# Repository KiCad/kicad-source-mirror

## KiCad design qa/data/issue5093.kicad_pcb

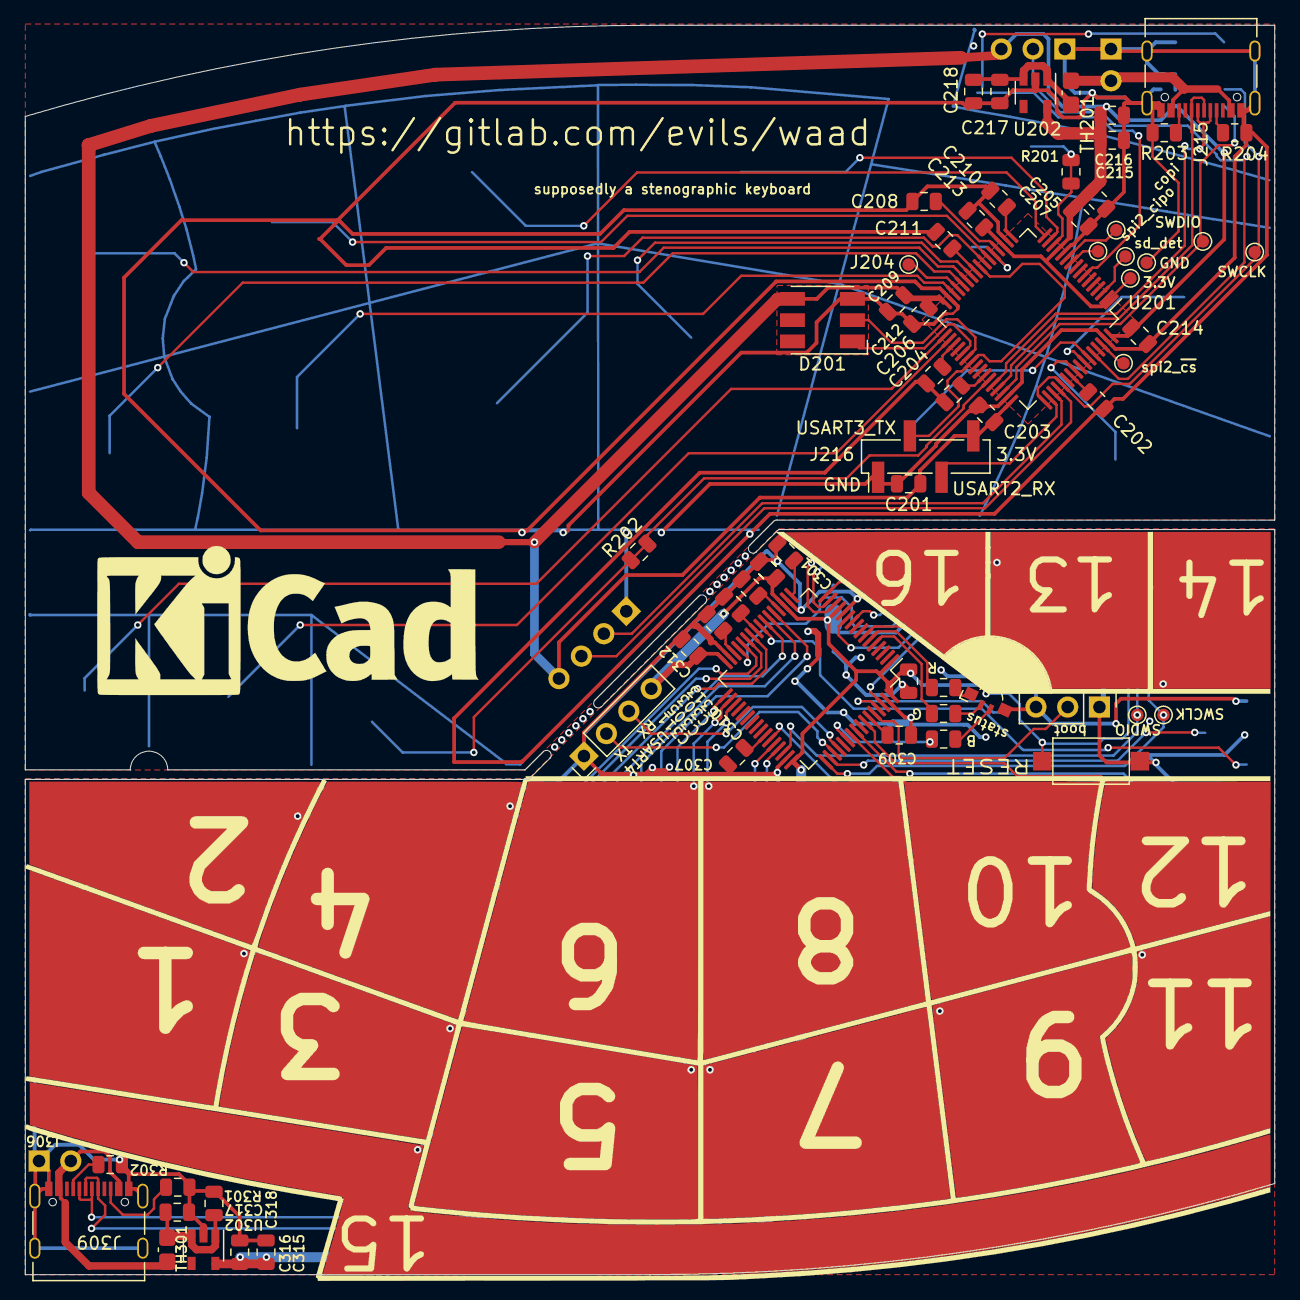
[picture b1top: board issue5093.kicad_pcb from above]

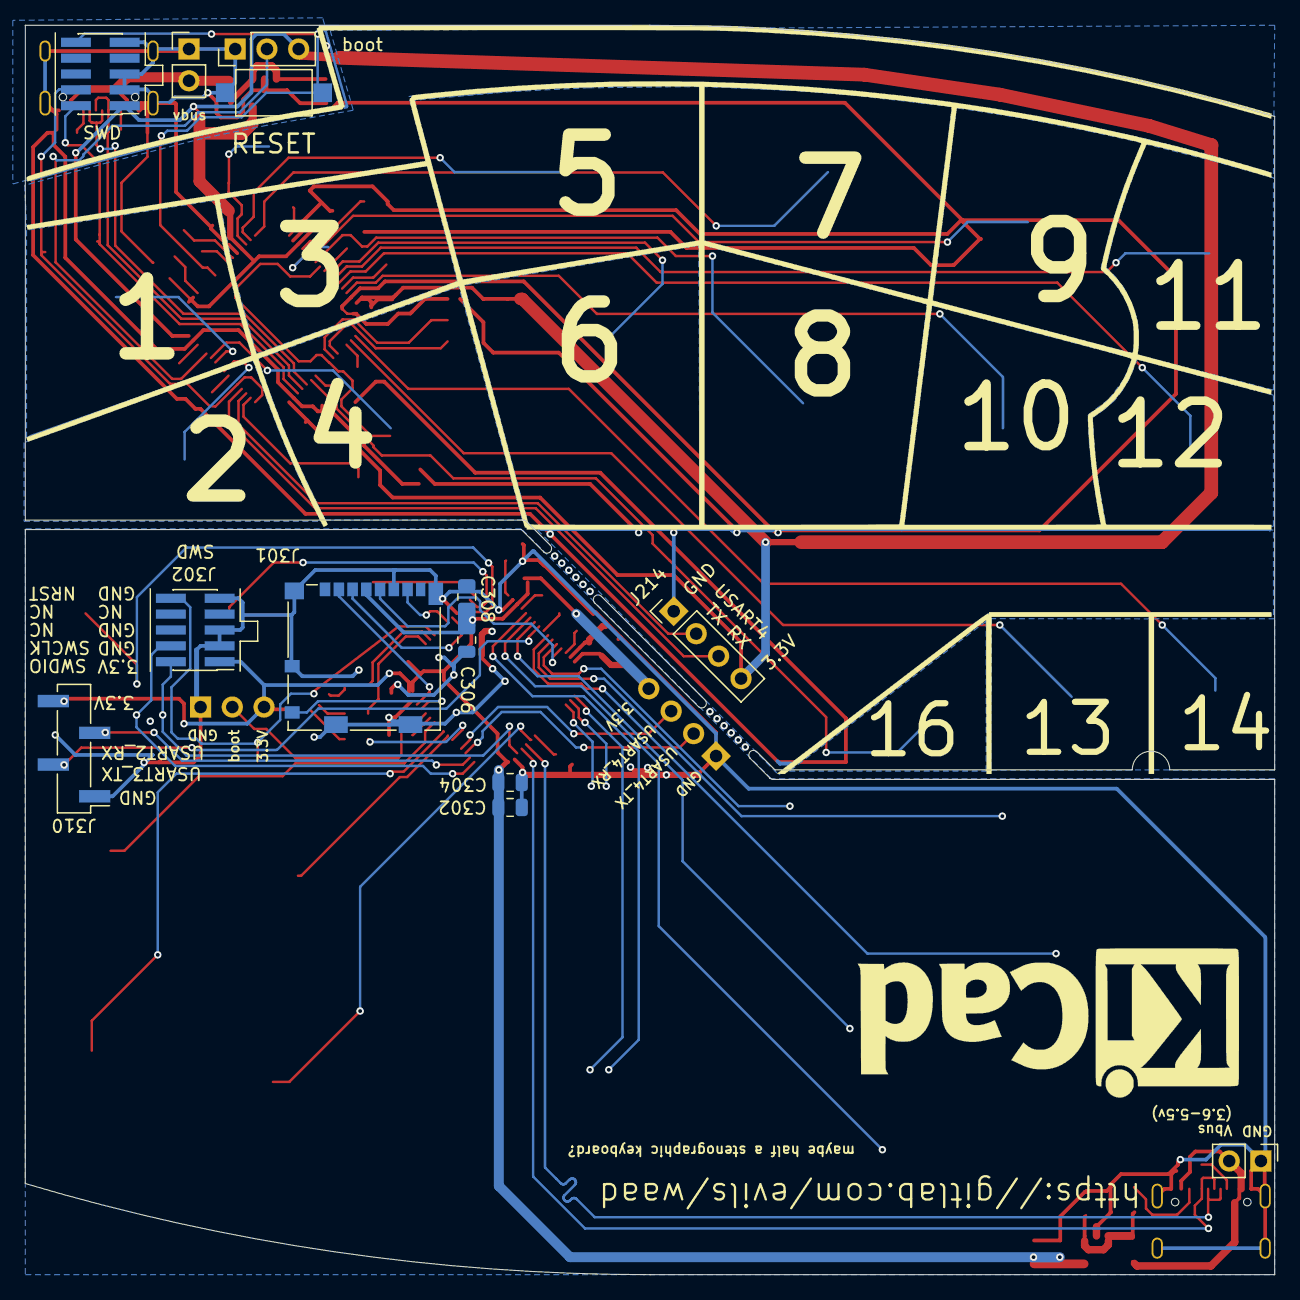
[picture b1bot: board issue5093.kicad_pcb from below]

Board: 2 copper layers, 100.0 x 100.0 mm, 81 parts (14 on the bottom side), 80 nets.

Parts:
C201, C209, C216, C217, C302, C310, C316, C317: 10µF; C_0805_2012Metric
C202, C204, C206, C208, C210, C211, C301, C303, C305, C307, C309, C311: C_Small; C_0805_2012Metric
C203, C205, C212, C213, C214, C304, C306, C312, C313, C314: 1µF; C_0805_2012Metric
C207, C308: 10nF; C_0805_2012Metric
C215, C218, C315, C318: 100µF; C_0805_2012Metric
D201: APA102; LED_RGB_5050-6
D301: LED_RABG; LED_Kingbright_APFA3010_3x1.5mm_Horizontal
J201, J202, J203, J204, J205, J206, J207, J209, J210, J303, J304: Conn_01x01_Male; TestPoint_Pad_D1.0mm
J208, J302: Conn_ARM_JTAG_SWD_10; PinHeader_2x05_P1.27mm_Vertical_SMD
J211: cap_pads; L_borders
J212, J306: Conn_01x02_Male; PinHeader_1x02_P2.54mm_Vertical
J213, J307: Conn_01x03_Male; PinHeader_1x03_P2.54mm_Vertical
J214, J308: Conn_01x04_Male; PinHeader_1x04_P2.54mm_Vertical
J215, J309: USB_C_Receptacle_USB2.0; USB_C_Receptacle_Palconn_UTC16-G
J216, J310: Conn_01x04_Male; PinHeader_1x04_P2.54mm_Vertical_SMD_Pin1Left
J301: Micro_SD_Card_Det; microSD_HC_Molex_104031-0811
J305: cap_pads; R_pads
R201, R202: 1k; R_0805_2012Metric
R203, R204, R301, R302: 5k1; R_0805_2012Metric
R303: 50; R_0805_2012Metric
R304, R305: 5; R_0805_2012Metric
SW201, SW301: SW_Push; SW_SPST_CK_RS282G05A3
TH201, TH301: Thermistor_PTC; Fuse_0805_2012Metric_Castellated
U201, U301: STM32F072R8Tx; LQFP-64_10x10mm_P0.5mm
U202, U302: TLV75533PDBV; SOT-23-5

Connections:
/left/+3V3: C201.1, C203.1, C205.1, C207.1, C209.1, C212.1, C213.1, C214.1, C215.1, C216.1, D201.4 (VCC), J203.1, J208.1 (VTref), J213.3, J214.4, J216.4, U201.1 (VBAT), U201.2 (PC13), U201.13 (VDDA), U201.19 (VDD), U201.32 (VDD), U201.48 (VDDIO2), U201.64 (VDD), U202.5 (OUT)
/left/APA_CI: D201.2 (CI), U201.38 (PC7)
/left/APA_DI: D201.1 (DI), U201.37 (PC6)
/left/BOOT0: J213.2, U201.60 (BOOT0)
/left/D+: J215.A6 (D+), J215.B6 (D+), U201.45 (PA12)
/left/D-: J215.A7 (D-), J215.B7 (D-), U201.44 (PA11)
/left/GND: C201.2, C202.2, C203.2, C204.2, C205.2, C206.2, C207.2, C208.2, C209.2, C210.2, C211.2, C212.2, C213.2, C214.2, C215.2, C216.2, C217.2, C218.2, D201.3 (GND), J205.1, J208.3 (GND), J208.5 (GND), J208.9 (GNDDetect), J212.1, J213.1, J214.1, J215.A1 (GND), J215.A12 (GND), J215.B1 (GND), J215.B12 (GND), J215.S1 (SHIELD), J216.1, R203.2, R204.2, SW201.1, U201.12 (VSSA), U201.18 (VSS), U201.31 (VSS), U201.47 (VSS), U201.63 (VSS), U202.2 (GND)
/left/NRST: J208.10 (~RESET~), SW201.2, U201.7 (NRST)
/left/P14: R201.1, R201.2, U201.14 (PA0)
/left/P17: C210.1, U201.17 (PA3)
/left/P20: C208.1, U201.20 (PA4)
/left/P25: C211.1, U201.25 (PC5)
/left/P35: C206.1, U201.35 (PB14)
/left/P42: C204.1, U201.42 (PA9)
/left/P43: R202.1, R202.2, U201.43 (PA10)
/left/P55: C202.1, U201.55 (PB3)
/left/SD_DET: J207.1, U201.3 (PC14)
/left/SPI2_CIPO: J206.1, U201.10 (PC2)
/left/SPI2_COPI: J202.1, U201.11 (PC3)
/left/SPI2_SCK: J204.1, U201.29 (PB10)
/left/SPI2_~CS: J201.1, U201.62 (PB9)
/left/SWCLK: J208.4 (SWDCLK/TCK), J210.1, U201.49 (PA14), U201.53 (PC12)
/left/SWDIO: J208.2 (SWDIO/TMS), J209.1, U201.46 (PA13)
/left/USART2_RX: J216.3, U201.50 (PA15)
/left/USART3_TX: J216.2, U201.24 (PC4), U201.39 (PC8)
/left/USART4_RX: J214.3, U201.52 (PC11)
/left/USART4_TX: J214.2, U201.51 (PC10)
/left/VBUS: J212.2, J215.A4 (VBUS), J215.A9 (VBUS), J215.B4 (VBUS), J215.B9 (VBUS), TH201.2
/right/+3V3: C302.1, C304.1, C306.1, C308.1, C310.1, C312.1, C313.1, C314.1, C315.1, C316.1, D301.2 (A), J301.4 (VDD), J302.1 (VTref), J307.3, J308.4, J310.4, U301.1 (VBAT), U301.13 (VDDA), U301.19 (VDD), U301.32 (VDD), U301.48 (VDDIO2), U301.64 (VDD), U302.5 (OUT)
/right/BOOT0: J307.2, U301.60 (BOOT0)
/right/D+: J309.A6 (D+), J309.B6 (D+), U301.45 (PA12)
/right/D-: J309.A7 (D-), J309.B7 (D-), U301.44 (PA11)
/right/GND: C301.2, C302.2, C303.2, C304.2, C305.2, C306.2, C307.2, C308.2, C309.2, C310.2, C311.2, C312.2, C313.2, C314.2, C315.2, C316.2, C317.2, C318.2, J301.6 (VSS), J301.9 (DET_B), J301.11 (SHIELD), J302.3 (GND), J302.5 (GND), J302.9 (GNDDetect), J306.1, J307.1, J308.1, J309.A1 (GND), J309.A12 (GND), J309.B1 (GND), J309.B12 (GND), J309.S1 (SHIELD), J310.1, R301.2, R302.2, SW301.1, U301.12 (VSSA), U301.18 (VSS), U301.31 (VSS), U301.47 (VSS), U301.63 (VSS), U302.2 (GND)
/right/LED_B: R305.1, U301.54 (PD2)
/right/LED_G: R304.1, U301.5 (PF0)
/right/LED_R: R303.1, U301.6 (PF1)
/right/NRST: J302.10 (~RESET~), SW301.2, U301.7 (NRST)
/right/P14: J305.14, U301.14 (PA0)
/right/P15: J305.13, U301.15 (PA1)
/right/P16: J305.16, U301.16 (PA2)
/right/P17: C301.1, U301.17 (PA3)
/right/P20: C303.1, U301.20 (PA4)
/right/P21: J305.5, U301.21 (PA5)
/right/P22: J305.15, U301.22 (PA6)
/right/P23: J305.3, U301.23 (PA7)
/right/P25: C305.1, U301.25 (PC5)
/right/P26: J305.1, U301.26 (PB0)
/right/P27: J305.2, U301.27 (PB1)
/right/P28: J305.4, U301.28 (PB2)
/right/P30: C311.1, U301.30 (PB11)
/right/P33: J305.7, U301.33 (PB12)
/right/P34: J305.6, U301.34 (PB13)
/right/P35: J305.8, U301.35 (PB14)
/right/P42: C307.1, U301.42 (PA9)
/right/P43: J305.9, U301.43 (PA10)
/right/P55: J305.10, U301.55 (PB3)
/right/P56: J305.11, U301.56 (PB4)
/right/P58: J305.12, U301.58 (PB6)
/right/P59: C309.1, U301.59 (PB7)
/right/SD_DET: J301.10 (DET_A), U301.61 (PB8)
/right/SPI2_CIPO: J301.7 (DAT0), U301.10 (PC2)
/right/SPI2_COPI: J301.3 (CMD), U301.11 (PC3)
/right/SPI2_SCK: J301.5 (CLK), U301.29 (PB10)
/right/SPI2_~CS: J301.2 (DAT3/CD), U301.62 (PB9)
/right/SWCLK: J302.4 (SWDCLK/TCK), J304.1, U301.49 (PA14)
/right/SWDIO: J302.2 (SWDIO/TMS), J303.1, U301.46 (PA13)
/right/USART2_RX: J310.3, U301.50 (PA15)
/right/USART3_TX: J310.2, U301.24 (PC4)
/right/USART4_RX: J308.3, U301.52 (PC11)
/right/USART4_TX: J308.2, U301.51 (PC10)
/right/VBUS: J306.2, J309.A4 (VBUS), J309.A9 (VBUS), J309.B4 (VBUS), J309.B9 (VBUS), TH301.2
unnamed: C217.1, C218.1, TH201.1, U202.1 (IN), U202.3 (EN)
unnamed: C317.1, C318.1, TH301.1, U302.1 (IN), U302.3 (EN)
unnamed: D301.1 (RK), R303.2
unnamed: D301.3 (BK), R305.2
unnamed: D301.4 (GK), R304.2
unnamed: J215.A5 (CC1), R204.1
unnamed: J215.B5 (CC2), R203.1
unnamed: J309.A5 (CC1), R302.1
unnamed: J309.B5 (CC2), R301.1

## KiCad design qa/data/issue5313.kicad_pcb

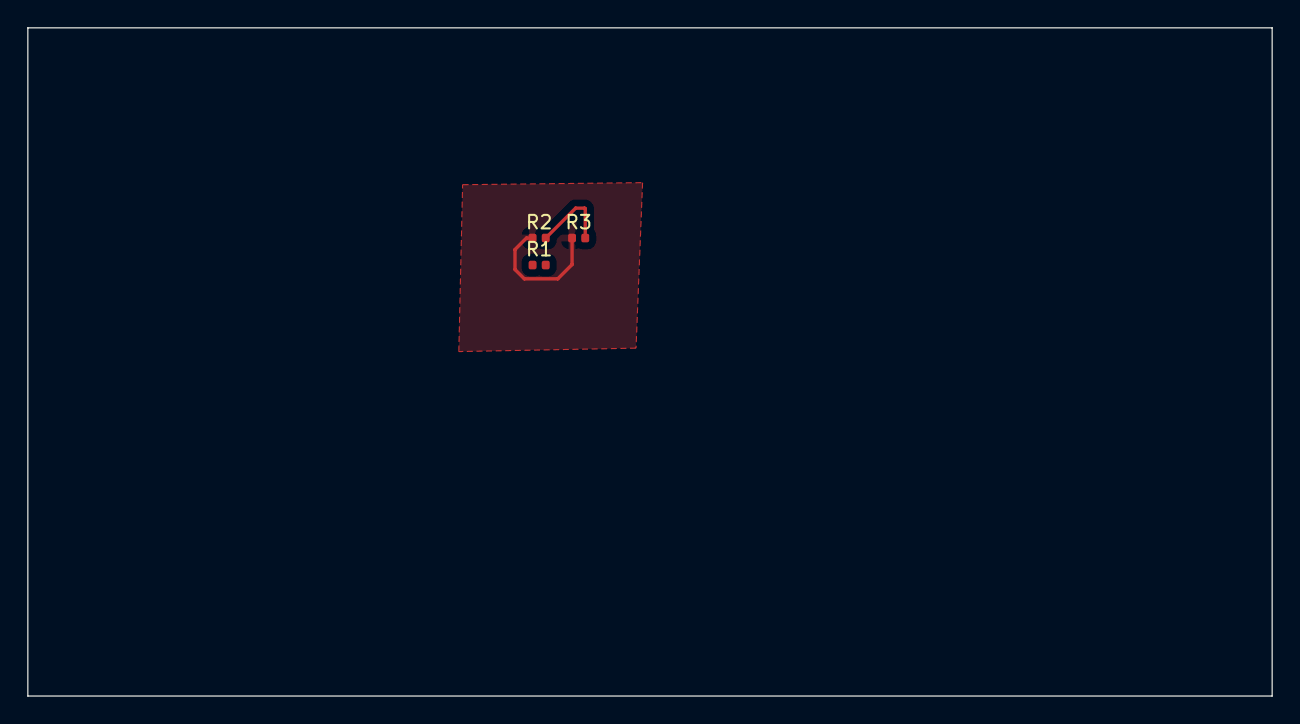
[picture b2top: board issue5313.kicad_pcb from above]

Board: 2 copper layers, 91.7 x 49.2 mm, 3 parts (0 on the bottom side), 2 nets.

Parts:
R1, R2, R3: R_Small; R_0402_1005Metric

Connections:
unnamed: R1.2, R2.2, R3.2
unnamed: R2.1, R3.1

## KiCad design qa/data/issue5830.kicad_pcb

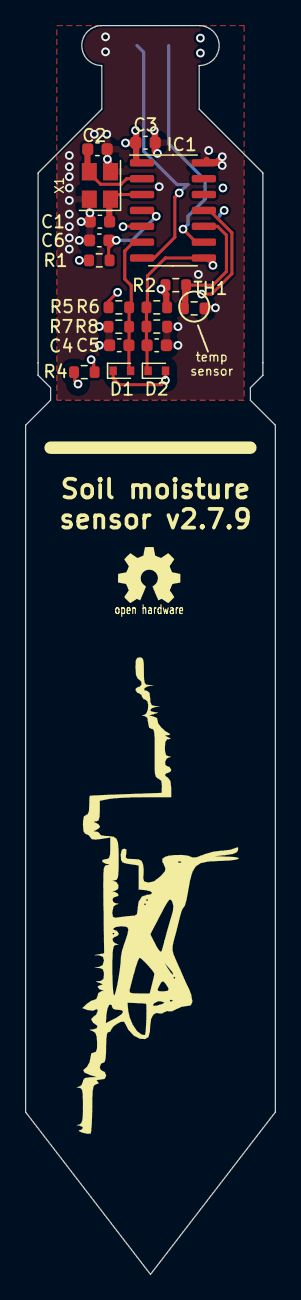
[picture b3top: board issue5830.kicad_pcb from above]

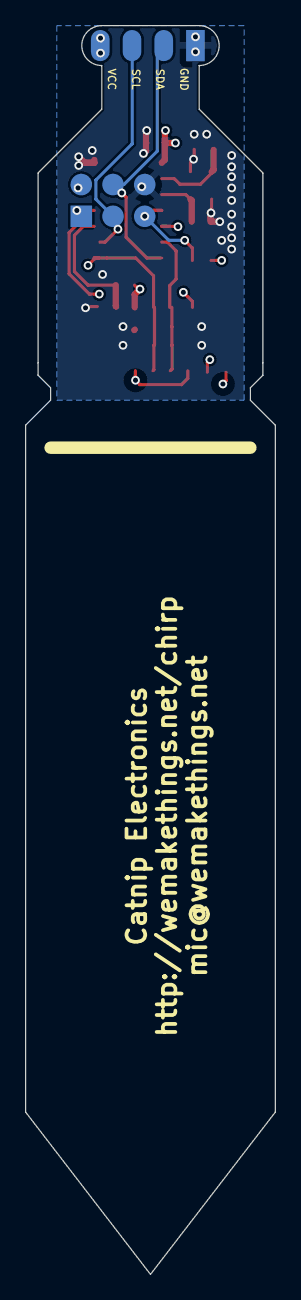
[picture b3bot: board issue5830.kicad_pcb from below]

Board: 4 copper layers, 20.0 x 100.0 mm, 20 parts (2 on the bottom side), 13 nets.

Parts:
C1: 33p; C_0603_1608Metric
C2: 33pp; C_0603_1608Metric
C3, C6: 1u; C_0603_1608Metric
C4, C5: 1n; C_0603_1608Metric
D1, D2: BAT54; D_SOD-523
IC1: ATTINY441-SSU; SOIC-14_3.9x8.7mm_P1.27mm
P1: CONN_02X03; Pin_Header_Straight_2x03
P2: CONN_01X04; Pin_Header_Straight_1x04_Pitch2.54mm
R1: 10k; R_0603_1608Metric
R2: 10k 0.1%; R_0603_1608Metric
R4: 330; R_0603_1608Metric
R5, R6, R7, R8: 1M; R_0603_1608Metric
TH1: NCP18XH103F03RB; R_0603_1608Metric
X1: 16MHz; Crystal_SMD_3225-4pin_3.2x2.5mm

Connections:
/EXCITATION: IC1.5, R4.2
/MISO/SENSE_HIGH: C5.1, D2.2, IC1.8, P1.1, R6.1, R8.2
/MOSI/SDA: IC1.7, P1.4, P2.2
/RESET: C6.1, IC1.4, P1.5, R1.1
/SCK/SCL: IC1.9, P1.3, P2.3
/SENSE_LOW: C4.1, D1.1, IC1.6, R5.1, R7.2
/SENSOR_TRACK: D1.2, D2.1, R4.1
/THERMISTOR: IC1.10, R2.2, TH1.1
GND: C1.2, C2.2, C3.2, C4.2, C5.2, C6.2, IC1.14, P1.6, P2.1, R7.1, R8.1, TH1.2, X1.2, X1.4
unnamed: C1.1, IC1.3, X1.1
unnamed: C2.1, IC1.2, X1.3
unnamed: IC1.11, R2.1, R5.2, R6.2
VCC: C3.1, IC1.1, P1.2, P2.4, R1.2

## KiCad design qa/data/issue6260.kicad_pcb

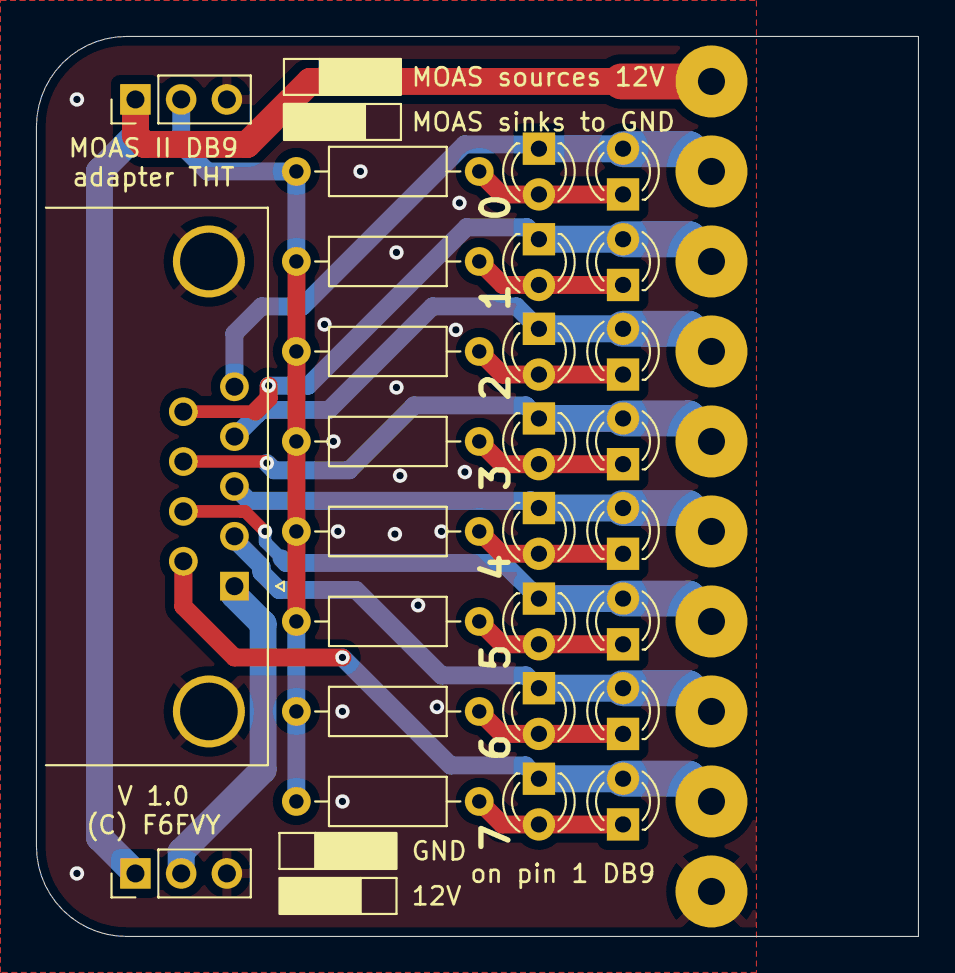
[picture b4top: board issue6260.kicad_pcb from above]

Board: 2 copper layers, 49.0 x 50.0 mm, 37 parts (0 on the bottom side), 20 nets.

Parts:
D1, D2, D3, D4, D5, D6, D7, D8, D9, D10, D11, D12, D13, D14, D15, D16: LED; LED_D3.0mm
J1, J2, J3, J4, J5, J6, J7, J8, J9, J10: Conn_01x01; SolderWirePad_1x01_Drill1.5mm
J11, J12: Conn_01x03; PinHeader_1x03_P2.54mm_Vertical
J13: DB9_Female_MountingHoles; DSUB-9_Female_Horizontal_P2.77x2.84mm_EdgePinOffset7.70mm_H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
R1, R2, R3, R4, R5, R6, R7, R8: 4k7; R_Axial_DIN0207_L6.3mm_D2.5mm_P10.16mm_Horizontal

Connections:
+12V: J1.1, J11.1, J12.1
GND: J10.1, J11.3, J12.3, J13.0 (PAD)
unnamed: D1.1 (K), D9.2 (A), J2.1, J13.5
unnamed: D1.2 (A), D9.1 (K), R1.1
unnamed: D2.2 (A), D10.1 (K), R2.1
unnamed: D2.1 (K), D10.2 (A), J3.1, J13.9
unnamed: D3.2 (A), D11.1 (K), R3.1
unnamed: D3.1 (K), D11.2 (A), J4.1, J13.4
unnamed: D4.2 (A), D12.1 (K), R4.1
unnamed: D4.1 (K), D12.2 (A), J5.1, J13.8
unnamed: D5.2 (A), D13.1 (K), R5.1
unnamed: D5.1 (K), D13.2 (A), J6.1, J13.3
unnamed: D6.2 (A), D14.1 (K), R6.1
unnamed: D6.1 (K), D14.2 (A), J7.1, J13.7
unnamed: D7.2 (A), D15.1 (K), R7.1
unnamed: D7.1 (K), D15.2 (A), J8.1, J13.2
unnamed: D8.2 (A), D16.1 (K), R8.1
unnamed: D8.1 (K), D16.2 (A), J9.1, J13.6
unnamed: J11.2, R1.2, R2.2, R3.2, R4.2, R5.2, R6.2, R7.2, R8.2
unnamed: J12.2, J13.1

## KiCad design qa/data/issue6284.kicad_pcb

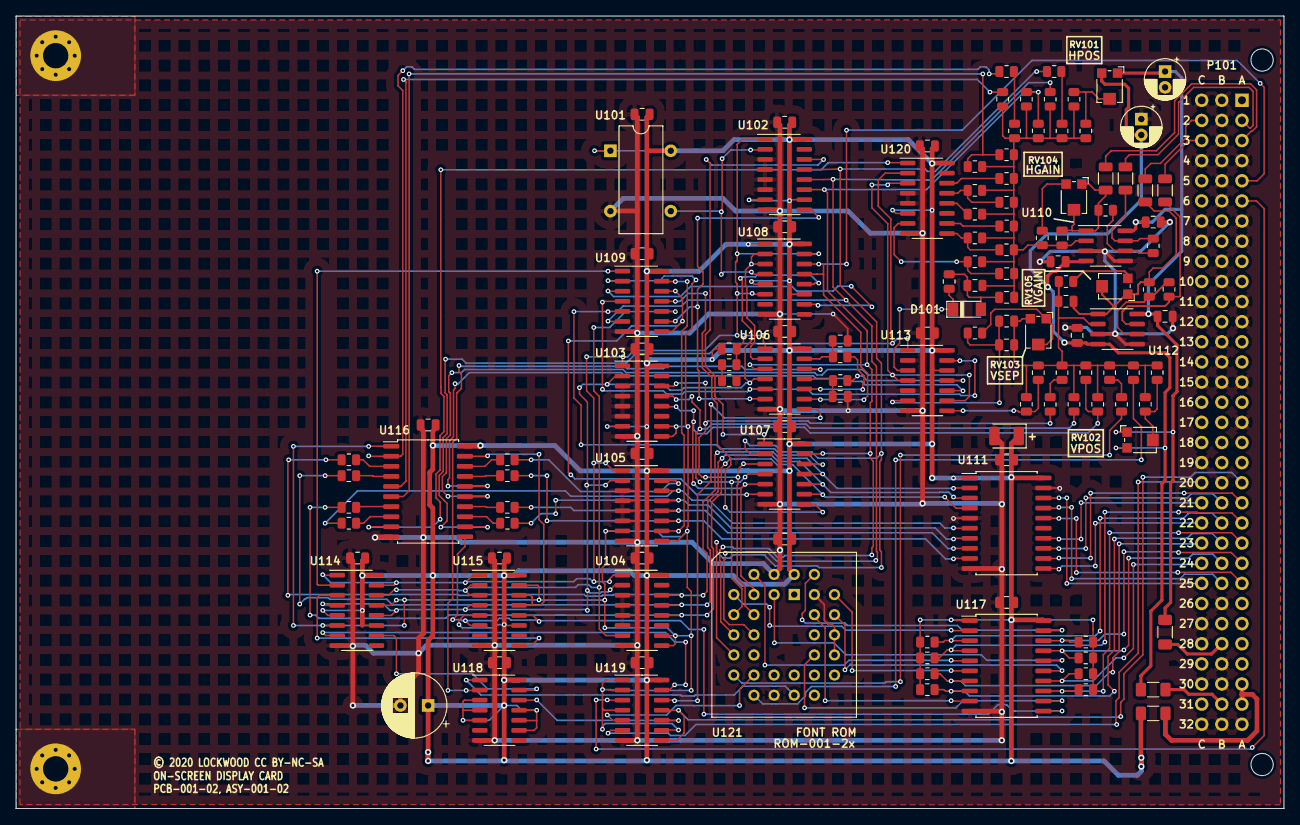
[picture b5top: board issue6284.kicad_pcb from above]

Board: 2 copper layers, 160.0 x 100.0 mm, 134 parts (0 on the bottom side), 127 nets.

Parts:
C101, C104, C105, C106, C108: 100p; C_0805_2012Metric
C102, C103: 47p; C_0805_2012Metric
C107, C109, C110: 330p; C_0805_2012Metric
CD101: 470µ; CP_Radial_D8.0mm_P3.50mm
CD102: 10µ; CP_EIA-3528-21_Kemet-B
CD103, CD104, CD105, CD106, CD107, CD108, CD109, CD110, CD111, CD112, CD113, CD114, CD115, CD116, CD117, CD118, CD119, CD120, CD121, CD123, CD124, CD126, CD127: 1µ; C_0805_2012Metric
CD122, CD125: 47µ; CP_Radial_D5.0mm_P2.00mm
D101: LL4448; D_MiniMELF
H101, H102: HOLE; MountingHole_3.2mm_M3_Pad_Via
P101: DIN41612_M_3x32_OS2; DIN41612_B_3x32_Horizontal
R101, R102, R103, R104, R105, R106, R107, R108, R155, R156: 2k37; R_0805_2012Metric
R109, R110, R112, R113, R114, R115, R116, R117, R118, R119, R128, R133, R137, R142, R143, R147, R148, R149, R150, R151: 39k; R_0805_2012Metric
R111, R120, R123, R125, R126: 1k96; R_0805_2012Metric
R121, R136: 680k; R_0805_2012Metric
R122, R129, R130, R131, R138, R152, R153, R154: 205k; R_0805_2012Metric
R124, R134, R135, R157, R158, R159, R160: 5k9; R_0805_2012Metric
R127, R132, R144, R145, R146: 274k; R_0805_2012Metric
R139, R140, R141: 9k76; R_0805_2012Metric
R161, R162, R163, R164: 1k5; R_1206_3216Metric
RT101, RT102, RT103: 250mA; R_1206_3216Metric_Pad1.30x1.75mm_HandSolder
RV101, RV102: 20k; Potentiometer_Bourns_TC33X_Vertical
RV103: 1k; Potentiometer_Bourns_TC33X_Vertical
RV104, RV105: 500; Potentiometer_Bourns_TC33X_Vertical
U101: 2MHz; Oscillator_SeikoEpson_SG-8002DC
U102, U103, U104, U105: 'HC161; SOIC-16_3.9x9.9mm_P1.27mm
U106: 'HC14; SOIC-14_3.9x8.7mm_P1.27mm
U107, U118: 'HC10; SOIC-14_3.9x8.7mm_P1.27mm
U108, U114, U115: 'HC109; SOIC-16_3.9x9.9mm_P1.27mm
U109: 'HC02; SOIC-14_3.9x8.7mm_P1.27mm
U110, U112: NE5532; SOIC-8_3.9x4.9mm_P1.27mm
U111: 'HC245; SOIC-20W_7.5x12.8mm_P1.27mm
U113: 'HC86; SOIC-14_3.9x8.7mm_P1.27mm
U116, U117: 'HCT273; SOIC-20W_7.5x12.8mm_P1.27mm
U119: 'HC03; SOIC-14_3.9x8.7mm_P1.27mm
U120: 'HC237; SOIC-16_3.9x9.9mm_P1.27mm
U121: 27C512; PLCC-32_THT-Socket

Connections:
+15V: CD122.1, CD123.1, CD124.1, RT101.2, RV101.1, RV102.1, U110.8 (V+), U112.8 (V+)
-15V: CD125.2, CD126.1, CD127.1, RT103.2, RV101.3, RV102.3, U110.4 (V-), U112.4 (V-)
/CHAR0: P101.B22 (CHAR0), R108.2, U117.3 (D0)
/CHAR1: P101.A22 (CHAR1), R107.2, U117.4 (D1)
/CHAR2: P101.C23 (CHAR2), R106.2, U117.7 (D2)
/CHAR3: P101.B23 (CHAR3), R105.2, U117.8 (D3)
/CHAR4: P101.A23 (CHAR4), R104.2, U117.13 (D4)
/CHAR5: P101.C24 (CHAR5), R103.2, U117.14 (D5)
/CHAR6: P101.B24 (CHAR6), R102.2, U117.17 (D6)
/CHAR7: P101.A24 (CHINT), R101.2, U117.18 (D7)
/Circuit/CHAR0: U117.2 (Q0), U121.5 (A6)
/Circuit/CHAR1: U117.5 (Q1), U121.4 (A7)
/Circuit/CHAR2: U117.6 (Q2), U121.29 (A8)
/Circuit/CHAR3: U117.9 (Q3), U121.28 (A9)
/Circuit/CHAR4: U117.12 (Q4), U121.24 (A10)
/Circuit/CHAR5: U117.15 (Q5), U121.27 (A11)
/Circuit/CHAR6: U117.16 (Q6), U121.3 (A12)
/Circuit/CHAR7: U117.19 (Q7), U121.30 (A13)
/Circuit/DESCENDER0: R129.2, U121.13 (O0)
/Circuit/DESCENDER1: R138.2, U121.14 (O1)
/Circuit/FINISH#: U114.3 (~K), U115.9 (~Q)
/Circuit/FINISHREQ: R119.2, U105.15 (Tc)
/Circuit/FLD0: U116.9 (Q3), U120.1 (A0)
/Circuit/FLD1: U113.1, U116.12 (Q4), U120.2 (A1)
/Circuit/FLD2: U113.4, U113.9, U116.15 (Q5), U120.3 (A2)
/Circuit/FLD3: U113.10, U116.16 (Q6)
/Circuit/FLDREQ0: R115.2, U105.14 (Q0), U111.6 (A4)
/Circuit/FLDREQ1: R116.2, U105.13 (Q1), U111.7 (A5)
/Circuit/FLDREQ2: R117.2, U105.12 (Q2), U111.8 (A6)
/Circuit/FLDREQ3: R118.2, U105.11 (Q3), U111.9 (A7)
/Circuit/FLD_BOTTOM: R136.1, R137.2, U113.8
/Circuit/HDOT0: R127.2, U102.13 (Q1), U107.2, U121.11 (A0)
/Circuit/HDOT1: R132.2, U102.12 (Q2), U109.6, U121.10 (A1)
/Circuit/HDOT2: R145.2, R146.2, U102.11 (Q3), U106.3, U107.13, U121.9 (A2)
/Circuit/INTEN: U119.5, U121.15 (O2)
/Circuit/INTERLINE_BLANK#: U106.12, U118.2
/Circuit/LASTDOT: U106.5, U109.4, U113.13
/Circuit/LATCHBUS: U115.6 (Q), U115.12 (C), U116.11 (Cp), U117.11 (Cp)
/Circuit/LINE0: R122.2, U103.14 (Q0), U107.3, U121.8 (A3)
/Circuit/LINE1: R153.2, U103.13 (Q1), U107.4, U121.7 (A4)
/Circuit/LINE2: R130.2, R131.2, U103.12 (Q2), U107.5, U121.6 (A5)
/Circuit/NEXTFLDREQ: U105.10 (ENT), U109.13
/Circuit/NEXTPOSREQ: U104.7 (ENP), U109.10, U114.14 (J), U115.2 (J), U115.3 (~K)
/Circuit/PIX_BLANK#: U118.1, U121.18 (O3)
/Circuit/POS0: R128.2, U116.2 (Q0)
/Circuit/POS1: R133.2, U116.5 (Q1)
/Circuit/POS2: R148.2, R149.2, U116.6 (Q2)
/Circuit/POSREQ0: R112.2, U104.14 (Q0), U107.11, U111.2 (A0)
/Circuit/POSREQ1: R113.2, U104.13 (Q1), U107.10, U111.3 (A1)
/Circuit/POSREQ2: R114.2, U104.12 (Q2), U107.9, U111.4 (A2)
/Circuit/READY: U114.10 (Q), U118.13
/Circuit/STARTCMD: U106.8, U119.12
/Circuit/~LASTDOT: U102.9 (~Pe), U106.6, U109.9
/Circuit/~LASTLINE: U107.6, U109.8, U109.12
/Circuit/~LASTPOSREQ: U107.8, U109.11
/FLD0: P101.C21 (SA12), U111.14 (B4)
/FLD1: P101.B21 (SA13), U111.13 (B5)
/FLD2: P101.A21 (SA14), U111.12 (B6)
/FLD3: P101.C22 (SA15), U111.11 (B7)
/H+: P101.A2 (TS+), R162.2
/H-: P101.A3 (TS-), R161.2
/INTEN#: P101.C20 (SA10), U119.6
/POS0: P101.C25 (POS0), U111.18 (B0)
/POS1: P101.B25 (POS1), U111.17 (B1)
/POS2: P101.A25 (POS2), U111.16 (B2)
/RUN#: P101.A6 (SS1), U119.3
/START#: P101.A5 (SS0), U106.9, U108.13 (~K), U108.14 (J)
/V+: P101.C2 (SIG+), R163.2
/V-: P101.C3 (SIG-), R164.2
/ZSEL: P101.A20 (SA11), U119.8, U119.11
DONE: U114.7 (~Q), U119.13
DOTCLK: U101.5 (OUT), U102.2 (CK), U108.4 (C)
GND: C102.2, C103.2, CD101.2, CD102.2, CD103.2, CD104.2, CD105.2, CD106.2, CD107.2, CD108.2, CD109.2, CD110.2, CD111.2, CD112.2, CD113.2, CD114.2, CD115.2, CD116.2, CD117.2, CD118.2, CD119.2, CD120.2, CD121.2, CD122.2, CD123.2, CD124.2, CD125.1, CD126.2, CD127.2, H101.1, H102.1, P101.A1 (GND), P101.A4 (GND), P101.A7 (GND), P101.A8 (GND), P101.A11 (GND), P101.A12 (GND), P101.A15 (GND), P101.A17 (GND), P101.A32 (GND), P101.B1 (GND), P101.B2 (GND), P101.B3 (GND), P101.B4 (GND), P101.B5 (GND), P101.B6 (GND), P101.B9 (GND), P101.B10 (GND), P101.B13 (GND), P101.B14 (GND), P101.B15 (GND), P101.B20 (GND), P101.B26 (GND), P101.B29 (GND), P101.B30 (GND), P101.B32 (GND), P101.C1 (GND), P101.C4 (GND), P101.C7 (GND), P101.C8 (GND), P101.C11 (GND), P101.C12 (GND), P101.C15 (GND), P101.C19 (GND), P101.C27 (GND), P101.C28 (GND), P101.C30 (GND), P101.C32 (GND), R110.2, U101.4 (GND), U102.3 (P0), U102.4 (P1), U102.5 (P2), U102.6 (P3), U102.8 (GND), U103.3 (P0), U103.4 (P1), U103.5 (P2), U103.6 (P3), U103.8 (GND), U104.3 (P0), U104.4 (P1), U104.5 (P2), U104.6 (P3), U104.8 (GND), U105.3 (P0), U105.4 (P1), U105.5 (P2), U105.6 (P3), U105.8 (GND), U106.7 (GND), U107.7 (GND), U108.8 (GND), U109.7 (GND), U110.3 (+), U110.5 (+), U111.5 (A3), U111.10 (GND), U111.19 (CE), U112.3 (+), U112.5 (+), U113.2, U113.5, U113.7 (GND), U114.8 (GND), U115.8 (GND), U116.10 (GND), U117.10 (GND), U118.7 (GND), U119.7 (GND), U120.4 (~LE), U120.5 (~E1), U120.8 (GND), U121.2 (A15), U121.16 (GND), U121.23 (~CE), U121.25 (~OE~/VPP), U121.31 (A14)
unnamed: C101.2, R109.1, U106.1
unnamed: C102.1, R111.1, U106.11
unnamed: C103.1, R120.1, U106.13
unnamed: C104.1, R126.2, U120.7 (Y7)
unnamed: C104.2, C107.2, C108.2, C109.1, R124.1, R125.1, R126.1, R132.1, R133.1, R134.1, R135.1, R139.1, R140.1, R141.1, R142.1, R143.1, R144.1, R145.1, R146.1, R147.1, R148.1, R149.1, R155.1, U110.2 (-)
unnamed: C105.1, C106.1, R123.2, U113.6
unnamed: C105.2, C106.2, C110.1, R130.1, R131.1, R136.2, R137.1, R138.1, R150.1, R151.1, R152.1, R153.1, R154.1, R156.1, RV103.3, U112.2 (-)
unnamed: C107.1, C108.1, D101.2 (A), R121.2
unnamed: C109.2, R157.1, R161.1, RV104.1, RV104.2, U110.1
unnamed: C110.2, R159.1, R163.1, RV105.1, RV105.2, U112.1
unnamed: D101.1 (K), R121.1, U113.3
unnamed: P101.A30 (+5V), P101.A31 (+5V), RT102.1
unnamed: P101.B28 (+15V), RT101.1
unnamed: P101.B31 (-15V), RT103.1
unnamed: R109.2, R110.1
unnamed: R111.2, U113.11
unnamed: R112.1, U116.3 (D0)
unnamed: R113.1, U116.4 (D1)
unnamed: R114.1, U116.7 (D2)
unnamed: R115.1, U116.8 (D3)
unnamed: R116.1, U116.13 (D4)
unnamed: R117.1, U116.14 (D5)
unnamed: R118.1, U116.17 (D6)
unnamed: R119.1, U116.18 (D7)
unnamed: R120.2, U106.10
unnamed: R122.1, R152.2
unnamed: R123.1, RV103.1, RV103.2
unnamed: R124.2, U120.14 (Y1)
unnamed: R125.2, U120.12 (Y3)
unnamed: R127.1, R144.2
unnamed: R128.1, R147.2
unnamed: R129.1, R154.2
unnamed: R134.2, R135.2, U120.13 (Y2)
unnamed: R139.2, U120.10 (Y5)
unnamed: R140.2, R141.2, U120.9 (Y6)
unnamed: R142.2, R143.2, RV101.2
unnamed: R150.2, R151.2, RV102.2
unnamed: R155.2, RV104.3
unnamed: R156.2, RV105.3
unnamed: R157.2, R158.2, U110.6 (-)
unnamed: R158.1, R162.1, U110.7
unnamed: R159.2, R160.2, U112.6 (-)
unnamed: R160.1, R164.1, U112.7
unnamed: U102.14 (Q0), U107.1
unnamed: U106.2, U108.2 (J), U108.3 (~K)
unnamed: U107.12, U109.5
unnamed: U108.10 (Q), U109.3
unnamed: U109.1, U114.2 (J)
unnamed: U115.13 (~K), U115.14 (J), U116.19 (Q7)
unnamed: U118.12, U119.10
POR#: U102.1 (~MR), U103.1 (~MR), U104.1 (~MR), U105.1 (~MR), U108.6 (Q), U108.15 (~R), U114.1 (~R), U114.15 (~R), U115.1 (~R)
REQCLK: U103.2 (CK), U104.2 (CK), U105.2 (CK), U106.4, U108.12 (C), U114.4 (C), U114.12 (C), U115.4 (C)
RUN: U103.9 (~Pe), U103.10 (ENT), U104.9 (~Pe), U104.10 (ENT), U105.7 (ENP), U105.9 (~Pe), U109.2, U114.6 (Q), U114.13 (~K), U115.15 (~R), U116.1 (~Mr), U119.1, U119.2, U119.4, U119.9
VCC: C101.1, CD101.1, CD102.1, CD103.1, CD104.1, CD105.1, CD106.1, CD107.1, CD108.1, CD109.1, CD110.1, CD111.1, CD112.1, CD113.1, CD114.1, CD115.1, CD116.1, CD117.1, CD118.1, CD119.1, CD120.1, CD121.1, R101.1, R102.1, R103.1, R104.1, R105.1, R106.1, R107.1, R108.1, RT102.2, U101.1 (OE), U101.8 (Vcc), U102.7 (ENP), U102.10 (ENT), U102.16 (VCC), U103.7 (ENP), U103.16 (VCC), U104.16 (VCC), U105.16 (VCC), U106.14 (VCC), U107.14 (VCC), U108.1 (~R), U108.5 (~S), U108.11 (~S), U108.16 (VCC), U109.14 (VCC), U111.1 (A->B), U111.20 (VCC), U113.12, U113.14 (VCC), U114.5 (~S), U114.11 (~S), U114.16 (VCC), U115.5 (~S), U115.11 (~S), U115.16 (VCC), U116.20 (VCC), U117.1 (~Mr), U117.20 (VCC), U118.3, U118.4, U118.5, U118.9, U118.10, U118.11, U118.14 (VCC), U119.14 (VCC), U120.6 (E2), U120.16 (VCC), U121.32 (VCC)

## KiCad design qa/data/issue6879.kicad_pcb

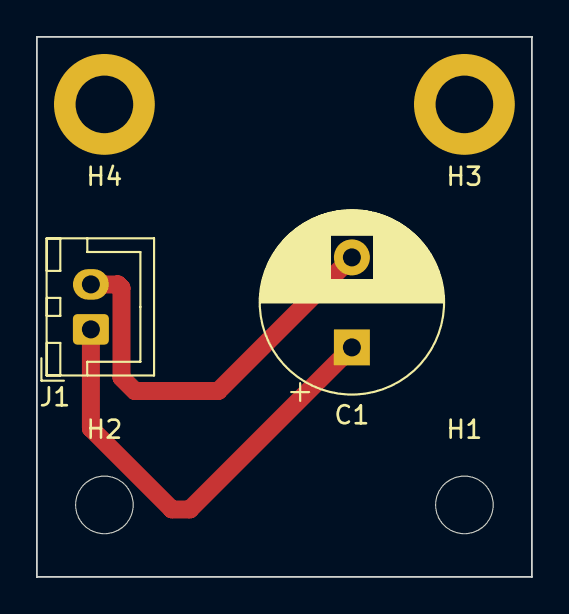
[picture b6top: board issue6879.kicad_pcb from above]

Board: 2 copper layers, 27.5 x 30.0 mm, 6 parts (0 on the bottom side), 2 nets.

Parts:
C1: 1m25vPY_5x10x16; CP_Radial_D10.0mm_P5.00mm
H1, H2: NPTH-3mm; MountingHole_3.2mm_M3
H3, H4: PTH-3mm; MountingHole_3.2mm_M3_DIN965_Pad
J1: XH-2A; JST_XH_B2B-XH-A_1x02_P2.50mm_Vertical

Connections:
unnamed: C1.1, J1.1
unnamed: C1.2, J1.2

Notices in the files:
qa/data/issue6284.kicad_pcb:
© 2020 LOCKWOOD CC BY-NC-SA
